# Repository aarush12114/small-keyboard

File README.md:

# aarush hackpad

aarush hackpad is a 9 key macropad with an OLED Display and uses KMK firmware

## Features:
- case to fit the keyboard
- 128x32 OLED Display
- visiblee XIAO because it looks cool
- 9 Keys

## CAD Model:
Everything fits together using 4 M3 Bolts.

it has 2 pieces 1 on which the pcb sits and another one at top to cover the pcb edges because i wanted to be able to see the pcb a little because it looks cool

Made in Fusion360.

## PCB
Here's my PCB! It was made in KiCad.

Schematic

PCB

## Firmware Overview
This hackpad uses [KMK](https://github.com/KMKfw) firmware for everything. 

- The 9 keys currently act as macros I dynamically change in VIA.
- The OLED is a cat!! Bongocat!! :3 (might not work yet will work in future)

I might add more in the future! That's it for now

## BOM:
Here should be everything you need to make this hackpad

- 9x Cherry MX Switches
- 9x DSA Keycaps
- 4x M3x5x4 Heatset inserts
- 3x M3x16mm SHCS Bolts
- 2X M3x12mm SHCS Bolts
- 10x 1N4148 DO-35 Diodes.
- 1x 0.91" 128x32 OLED Display
- 1x XIAO RP2040
- 1x Case (2 printed parts)

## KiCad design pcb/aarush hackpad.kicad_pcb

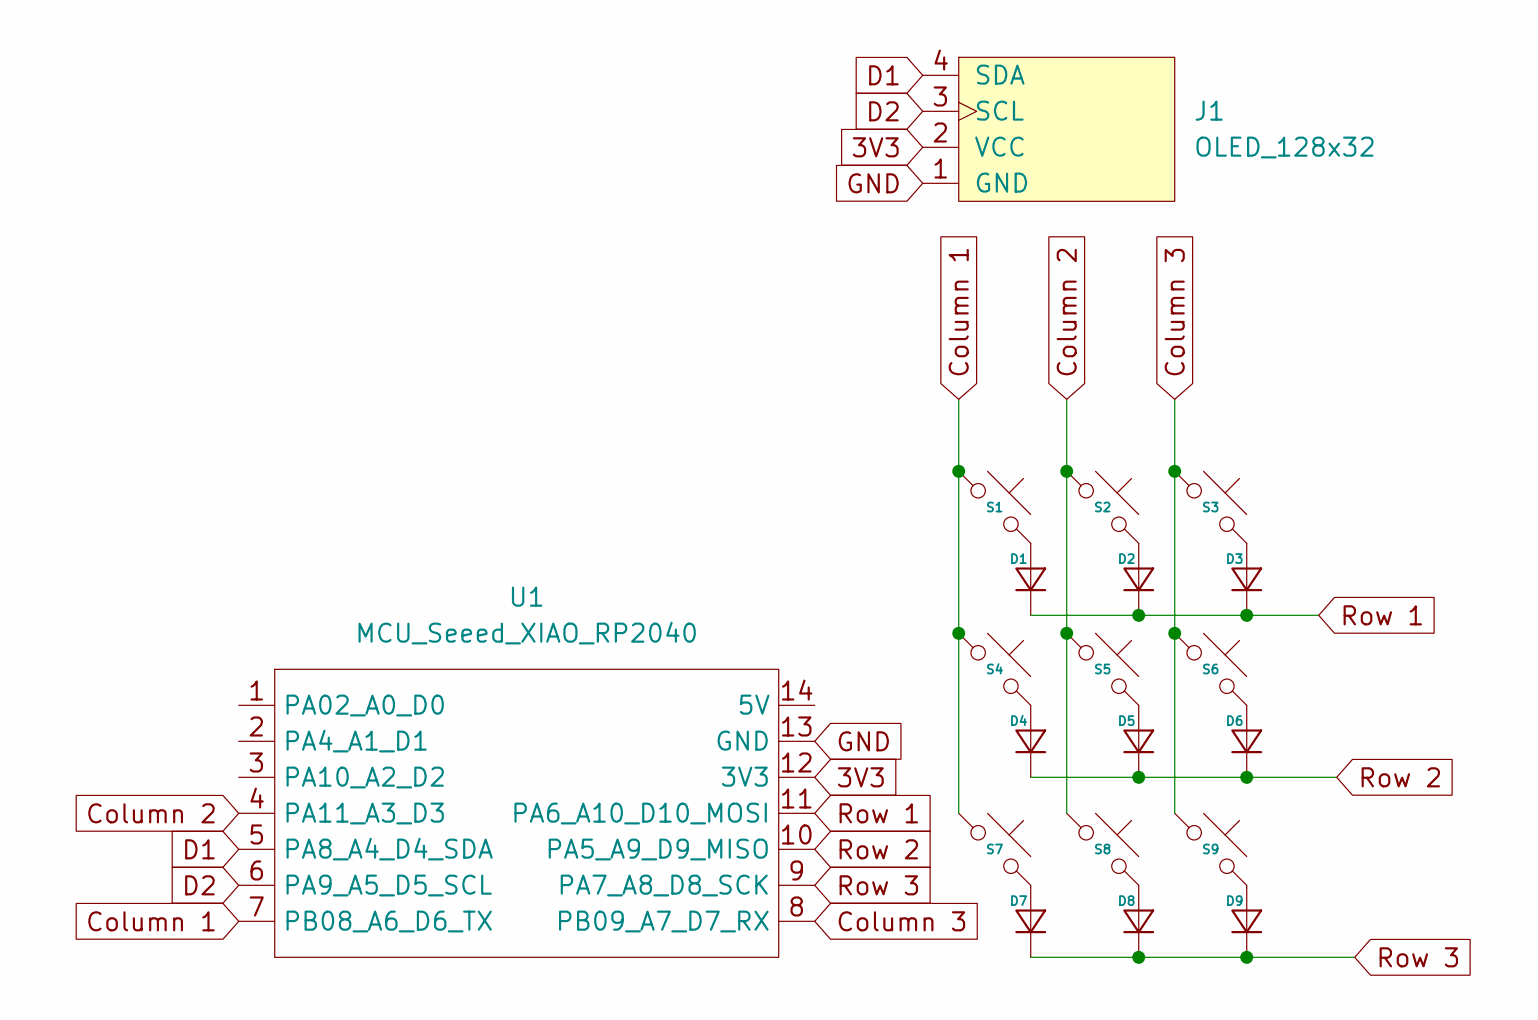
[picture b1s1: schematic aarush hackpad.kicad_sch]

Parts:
D1, D2, D3, D4, D5, D6, D7, D8, D9: Diode_DO-35
J1: OLED_128x32
S1, S2, S3, S4, S5, S6, S7, S8, S9: MX_PCB_1.00u
U1: MCU_Seeed_XIAO_RP2040; Seeed_XIAO_RP2040

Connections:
3V3: J1.2 (VCC), U1.12 (3V3)
Column 1: S1.1, S4.1, S7.1, U1.7 (PB08_A6_D6_TX)
Column 2: S2.1, S5.1, S8.1, U1.4 (PA11_A3_D3)
Column 3: S3.1, S6.1, S9.1, U1.8 (PB09_A7_D7_RX)
D1: J1.4 (SDA), U1.5 (PA8_A4_D4_SDA)
D2: J1.3 (SCL), U1.6 (PA9_A5_D5_SCL)
GND: J1.1 (GND), U1.13 (GND)
unnamed: D1.2 (A), S1.2
unnamed: D2.2 (A), S2.2
unnamed: D3.2 (A), S3.2
unnamed: D4.2 (A), S4.2
unnamed: D5.2 (A), S5.2
unnamed: D6.2 (A), S6.2
unnamed: D7.2 (A), S7.2
unnamed: D8.2 (A), S8.2
unnamed: D9.2 (A), S9.2
Row 1: D1.1 (K), D2.1 (K), D3.1 (K), U1.11 (PA6_A10_D10_MOSI)
Row 2: D4.1 (K), D5.1 (K), D6.1 (K), U1.10 (PA5_A9_D9_MISO)
Row 3: D7.1 (K), D8.1 (K), D9.1 (K), U1.9 (PA7_A8_D8_SCK)

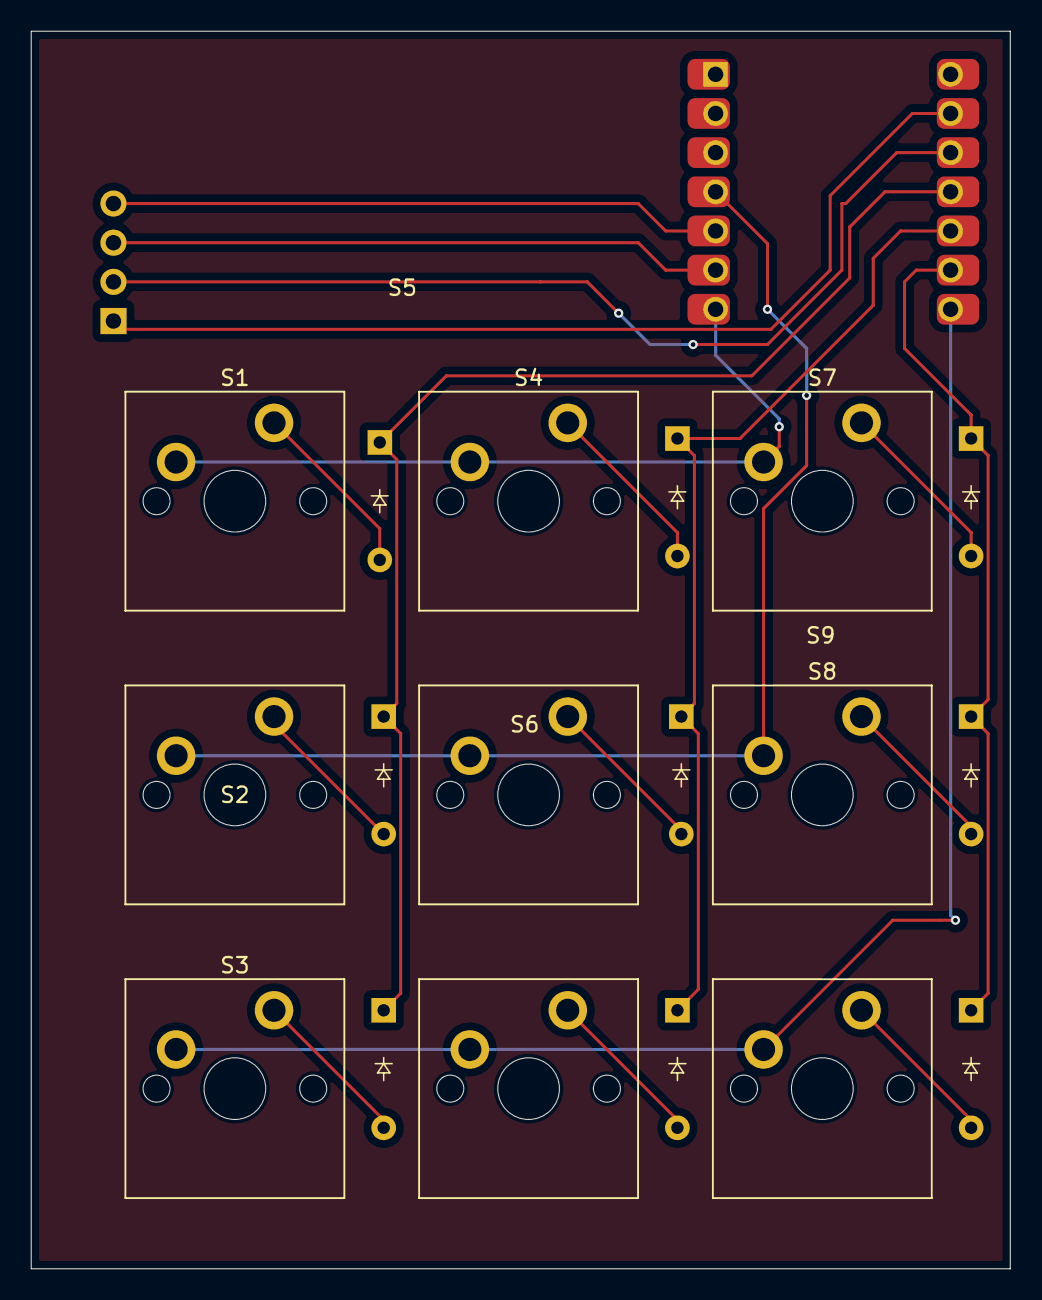
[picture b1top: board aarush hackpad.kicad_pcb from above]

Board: 2 copper layers, 63.5 x 80.3 mm, 20 parts (0 on the bottom side), 19 nets.
